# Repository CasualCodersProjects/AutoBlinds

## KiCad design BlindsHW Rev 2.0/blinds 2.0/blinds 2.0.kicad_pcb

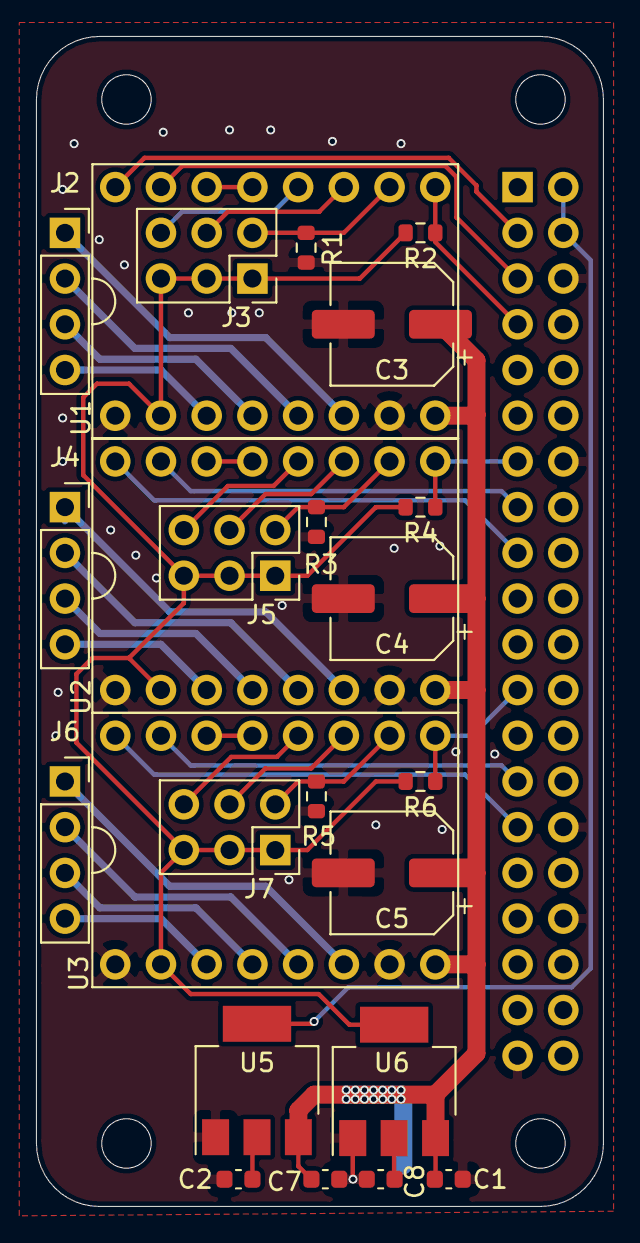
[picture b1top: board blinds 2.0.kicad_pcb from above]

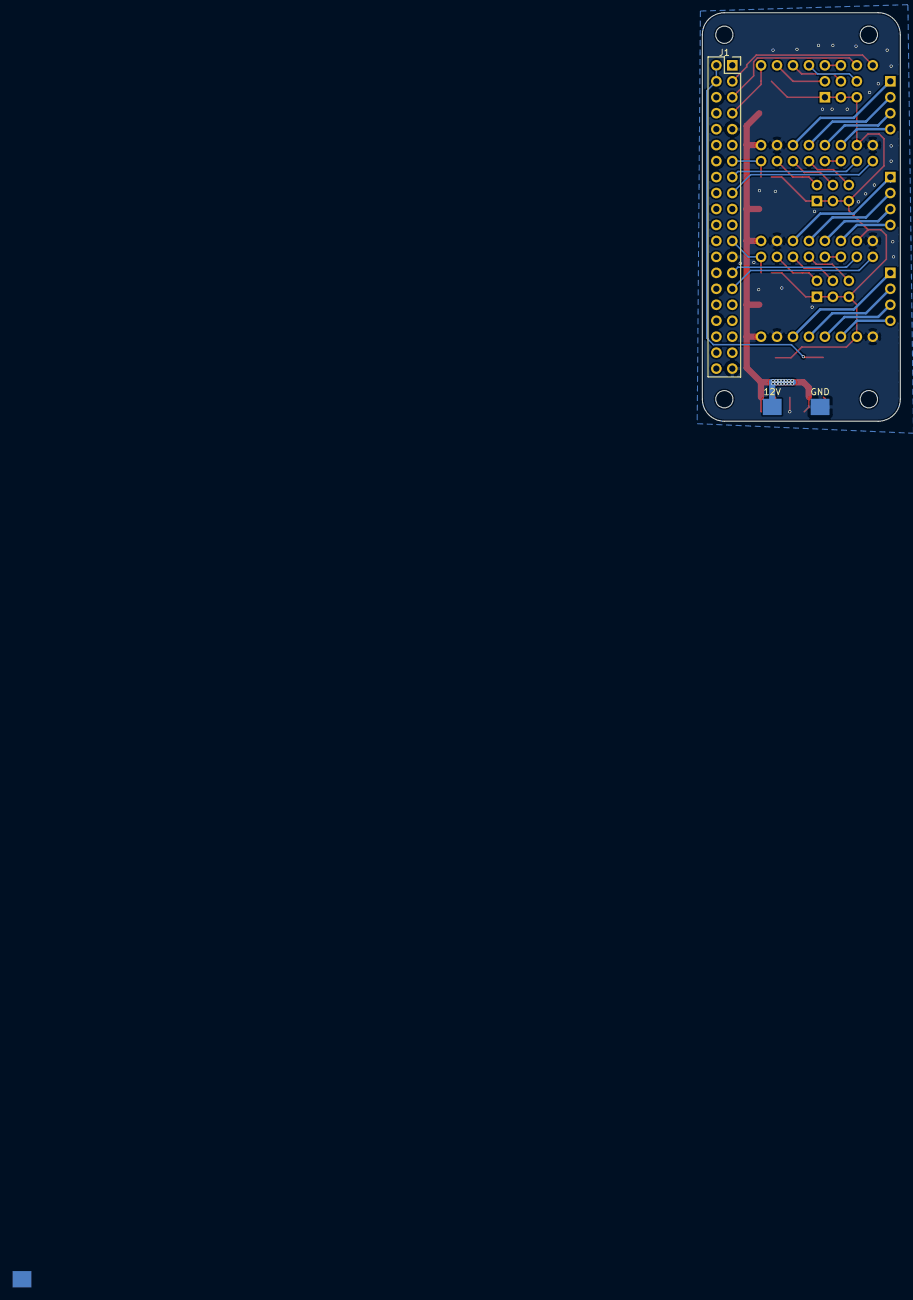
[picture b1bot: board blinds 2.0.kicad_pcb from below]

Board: 2 copper layers, 31.5 x 65.0 mm, 27 parts (3 on the bottom side), 37 nets.

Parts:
12V: Pin_D1.3mm_L11.0mm
C1, C2, C7, C8: C; C_0603_1608Metric
C3, C4, C5: CP1; CP_Elec_6.3x7.7
GND: Pin_D1.3mm_L11.0mm
J1: Conn_02x20_Odd_Even; PinSocket_2x20_P2.54mm_Vertical
J2, J4, J6: Conn_01x04; PinSocket_1x04_P2.54mm_Vertical
J3, J5, J7: Conn_02x03_Odd_Even; PinSocket_2x03_P2.54mm_Vertical
R1, R3, R5: 100k; R_0603_1608Metric
R2, R4, R6: 10k; R_0603_1608Metric
U1, U2, U3: a4988
U5: IFX27001TFV50; SOT-223-3_TabPin2
U6: AP1117-33; SOT-223-3_TabPin2

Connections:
+5V: C2.1, J1.2, J1.4, U5.2
+12V: 12V.1, C1.1, C3.1, C4.1, C5.1, C7.1, U1.9, U2.9, U3.9, U5.3, U6.3
/dir1: J1.3, U1.1
/dir2: J1.17, U2.1
/dir3: J1.29, U3.1
/en1: J1.7, R2.1, U1.8
/en2: J1.13, R4.1, U2.8
/en3: J1.23, R6.1, U3.8
/step1: J1.5, U1.2
/step2: J1.15, U2.2
/step3: J1.27, U3.2
GND: C1.2, C2.2, C3.2, C4.2, C5.2, C7.2, C8.2, GND.1, J1.6, J1.9, J1.14, J1.25, J1.30, J1.34, J1.39, R1.1, R3.1, R5.1, U1.10, U1.16, U2.10, U2.16, U3.10, U3.16, U5.1, U6.1
unnamed: J2.1, U1.11
unnamed: J2.2, U1.12
unnamed: J2.3, U1.13
unnamed: J2.4, U1.14
unnamed: J3.2, R1.2, U1.7
unnamed: J3.4, U1.6
unnamed: J3.6, U1.5
unnamed: J4.1, U2.11
unnamed: J4.2, U2.12
unnamed: J4.3, U2.13
unnamed: J4.4, U2.14
unnamed: J5.2, R3.2, U2.7
unnamed: J5.4, U2.6
unnamed: J5.6, U2.5
unnamed: J6.1, U3.11
unnamed: J6.2, U3.12
unnamed: J6.3, U3.13
unnamed: J6.4, U3.14
unnamed: J7.2, R5.2, U3.7
unnamed: J7.4, U3.6
unnamed: J7.6, U3.5
unnamed: U1.3, U1.4
unnamed: U2.3, U2.4
unnamed: U3.3, U3.4
VCC: C8.1, J3.1, J3.3, J3.5, J5.1, J5.3, J5.5, J7.1, J7.3, J7.5, R2.2, R4.2, R6.2, U1.15, U2.15, U3.15, U6.2

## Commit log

2022-06-04 Repo created, initial commit, very basic layout complete
2022-06-04 good enough for tonight. Gets the idea across.
2022-06-04 switched to components. Looks good ish
2022-06-05 Layout basically complete. Begin skinning
2022-06-05 styling mostly done. Still needs arrows in the number boxes and a better switch coloration
2022-06-11 began work on scheudling of motor control
2022-07-22 created fully new app. added json parsing stuffs
2022-07-22 Got Schedule server/client functional
2022-07-22 Cleaned up a bit
